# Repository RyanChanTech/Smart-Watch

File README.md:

# Smart-Watch
A smart watch project based off of the ESP32 microcontroller that I work on in my spare time. <br>
More info here: [https://ryanchantech.github.io/project_pages/smartwatch.html](https://ryanchantech.github.io/project_pages/smartwatch.html)

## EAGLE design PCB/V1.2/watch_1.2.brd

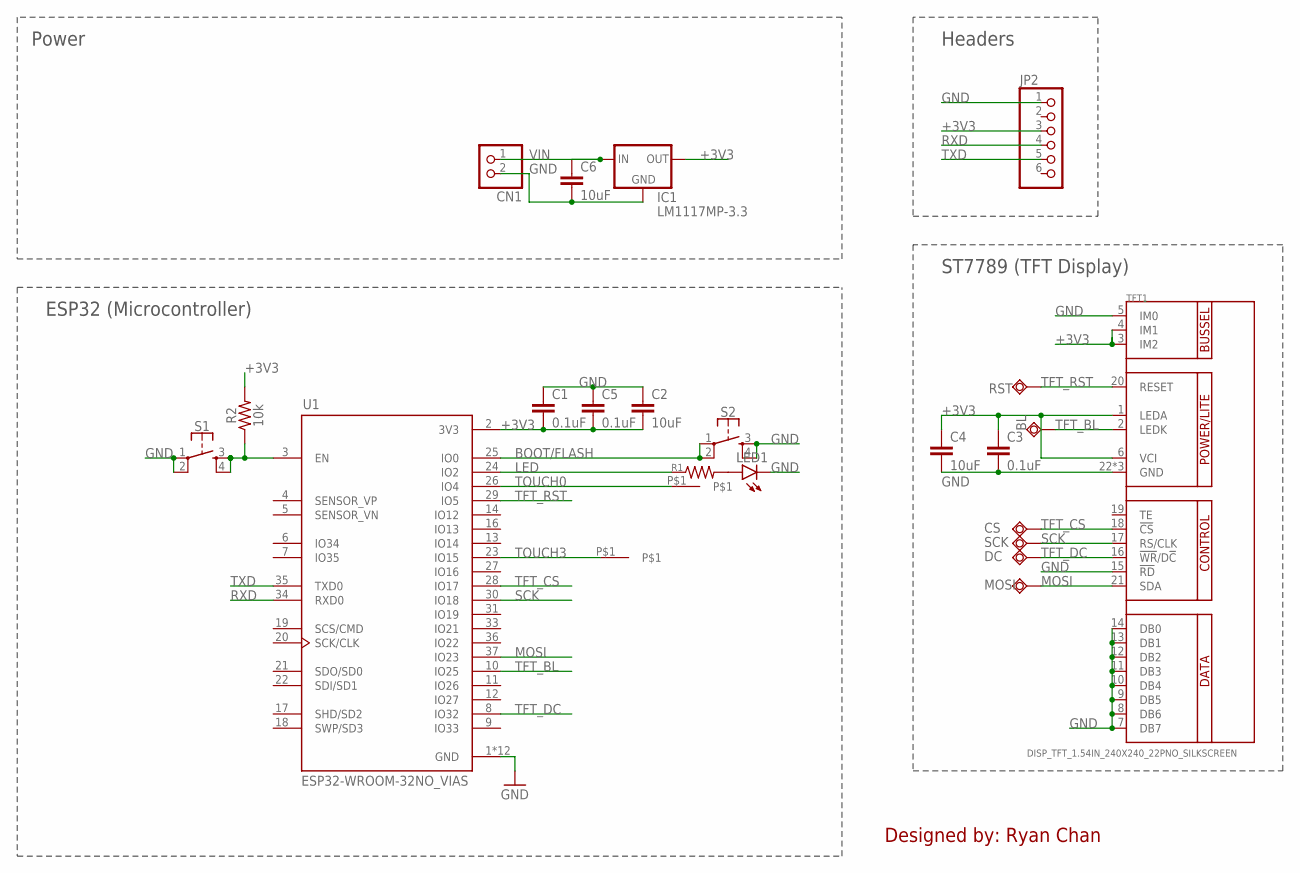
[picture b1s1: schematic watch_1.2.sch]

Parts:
BL: TPSQTP20R; TP20R
C1, C3, C5: 0.1uF; C0603
C2, C4, C6: 10uF; C0603
CN1: JST_2PIN-SMT-RA; JST-PH-2-SMT-RA
CS: TPSQTP20R; TP20R
DC: TPSQTP20R; TP20R
IC1: LM1117MP-3.3; SOT223
JP2: PINHD-1X6CLEAN; 1X06-CLEAN
LED1: LEDCHIPLED_0603; CHIPLED_0603
MOSI: TPSQTP20R; TP20R
R1: R-US_R0603; R0603
R2: 10k; 0603
RST: TPSQTP20R; TP20R
S1, S2: RESET; TACTILE_SWITCH_SMD_4.6X2.8MM
SCK: TPSQTP20R; TP20R
TFT1: DISP_TFT_1.54IN_240X240_22PNO_SILKSCREEN; TFT_1.54IN_240X240_22PIN_NO_SILKSCREEN
U1: ESP32-WROOM-32NO_VIAS; MODULE_ESP32-WROOM-32_NO_VIAS
U$1, U$2: CAPACITIVE_PAD_1

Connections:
+3V3: C1.2, C2.2, C3.1, C4.1, C5.2, IC1.2 (OUT), IC1.4 (OUT), JP2.3, R2.2, TFT1.1 (LEDA), TFT1.3 (IM2), TFT1.4 (IM1), TFT1.6 (VCI), U1.2 (3V3)
BOOT/FLASH: S2.1, S2.2, U1.25 (IO0)
CHIP_PU: R2.1, S1.3, S1.4, U1.3 (EN)
GND: C1.1, C2.1, C3.2, C4.2, C5.1, C6.2, CN1.2 (1), IC1.1 (GND), JP2.1, LED1.C, S1.1, S1.2, S2.3, S2.4, TFT1.5 (IM0), TFT1.7 (DB7), TFT1.8 (DB6), TFT1.9 (DB5), TFT1.10 (DB4), TFT1.11 (DB3), TFT1.12 (DB2), TFT1.13 (DB1), TFT1.14 (DB0), TFT1.15 (!RD), TFT1.22 (GND), TFT1.SUPPORT1 (GND), TFT1.SUPPORT2 (GND), U1.1 (GND), U1.15 (GND), U1.38 (GND), U1.39_1 (GND), U1.39_2 (GND), U1.39_3 (GND), U1.39_4 (GND), U1.39_5 (GND), U1.39_6 (GND), U1.39_7 (GND), U1.39_8 (GND), U1.39_9 (GND)
LED: R1.1, U1.24 (IO2)
MOSI: MOSI.TP, TFT1.21 (SDA), U1.37 (IO23)
unnamed: LED1.A, R1.2
RXD: JP2.4, U1.34 (RXD0)
SCK: SCK.TP, TFT1.17 (RS/CLK), U1.30 (IO18)
TFT_BL: BL.TP, TFT1.2 (LEDK), U1.10 (IO25)
TFT_CS: CS.TP, TFT1.18 (!CS), U1.28 (IO17)
TFT_DC: DC.TP, TFT1.16 (!WR!/D!C), U1.8 (IO32)
TFT_RST: RST.TP, TFT1.20 (RESET), U1.29 (IO5)
TOUCH0: U1.26 (IO4), U$2.P$1
TOUCH3: U1.23 (IO15), U$1.P$1
TXD: JP2.5, U1.35 (TXD0)
VIN: C6.1, CN1.1 (2), IC1.3 (IN)

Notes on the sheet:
Power
Headers
ESP32 (Microcontroller)
ST7789 (TFT Display)
Designed by: Ryan Chan

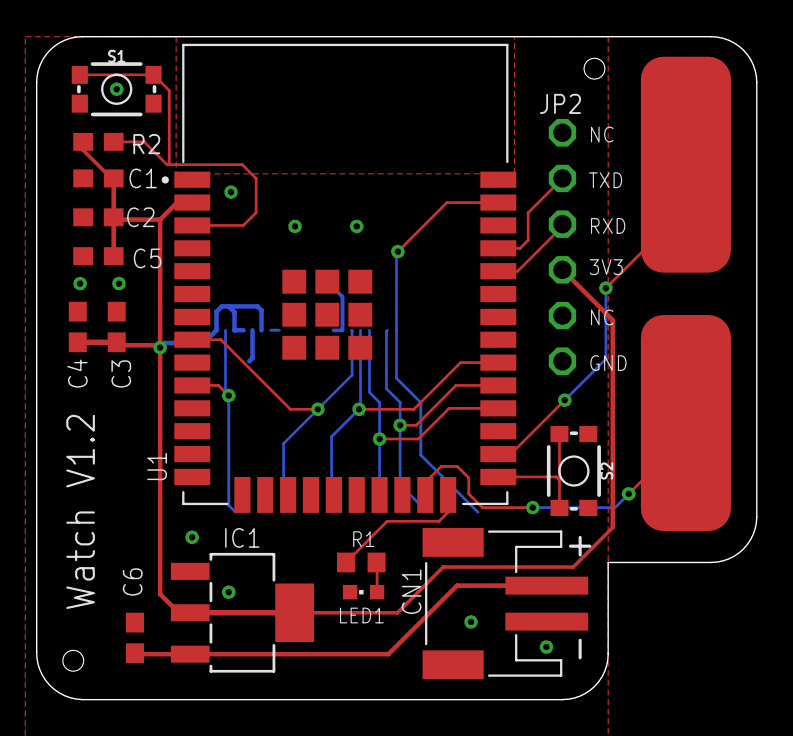
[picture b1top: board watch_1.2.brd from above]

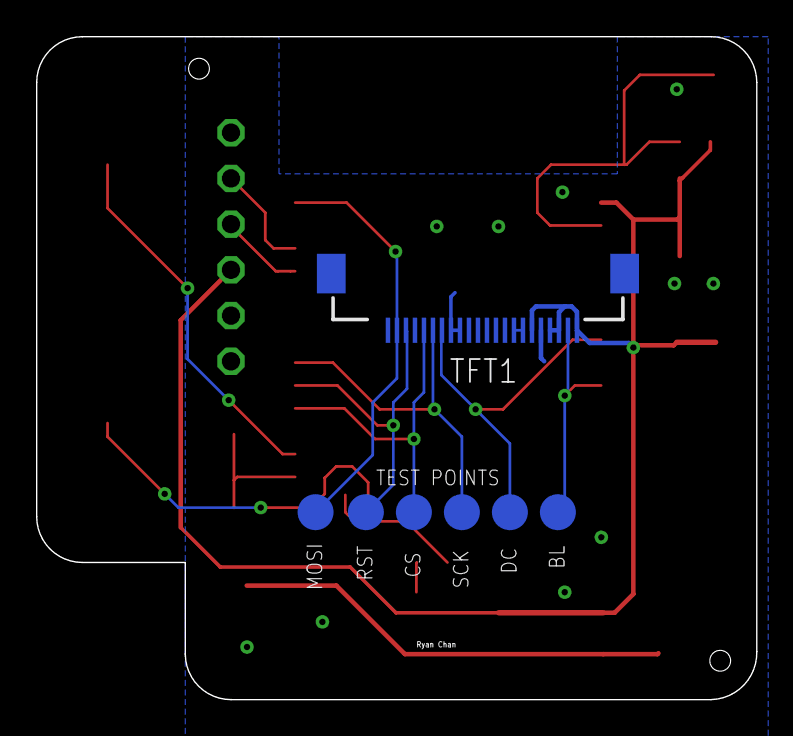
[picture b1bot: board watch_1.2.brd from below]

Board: 2 copper layers, 40.0 x 36.8 mm, 24 parts (6 on the bottom side), 17 nets.

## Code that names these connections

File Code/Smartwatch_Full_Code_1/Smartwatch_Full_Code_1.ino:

// TODO: run new JSON parser with old API link

/*
 * Code written by Ryan Chan
 * WiFi and OpenWeather portion based on code from Random Nerd Tutorials: https://randomnerdtutorials.com/esp32-http-get-open-weather-map-thingspeak-arduino/
 * 
 * To use this, you much install these libraries from the Arduino Library Manager:
 * Arduino_JSON
 * TimeLib
 * Adafruit_GFX
 * Adafruit BusIO
 * Adafruit Zero DMA
 * Adafruit ST7735 and ST7789
 * Adafruit SPIFlash
 */

//include Wifi libraries. to disable, go to places with "@"
#include <WiFi.h>
#include <HTTPClient.h>
#include <ArduinoJson.h>

//include TFT Display libraries
#include <Adafruit_GFX.h>    // Core graphics library
#include <Adafruit_ST7789.h> // Hardware-specific library for ST7789
#include <SPI.h>

#include <TimeLib.h>

//include fonts
#include <Fonts/FreeSansBoldOblique24pt7b.h>
#include <Fonts/FreeSansBoldOblique12pt7b.h>
#include <Fonts/FreeSans12pt7b.h>
#include <Fonts/FreeSansOblique9pt7b.h >
#include <Fonts/FreeSansOblique12pt7b.h >

const char* ssid = "yourWifiNameHere";
const char* password = "yourPasswordHere";

// Your Domain name with URL path or IP address with path
String openWeatherMapApiKey = "your API key here";

// Replace with your country code and city
String latitude = "your latitude here";
String longitude = "your longitude here";

int weatherUpdateInterval = 30; // the number of minutes before the weather data automatically updates

const int TFT_CS = 17;
const int TFT_RST = 5;
const int TFT_DC = 32;
const int TFT_BL = 25;

Adafruit_ST7789 tft = Adafruit_ST7789(TFT_CS, TFT_DC, TFT_RST);

unsigned long last_time;

String weekdays[] = {"Monday","Tuesday","Wednesday","Thursday","Friday","Saturday","Sunday"};

int seconds = 0;
int minutes = 0;
int hours = 0;
int days = 0;

void calculate_times(){
  if(seconds == 60){
    minutes++;
    seconds = 0;
  }
  
  if( minutes == 60 ){
    hours++;
    minutes = 0;
  }

  if(hours == 24){
    days++;
    hours = 0;
  }
}

// prepending 0's needs... alot of work..
String getFormattedHHMM(){
  String formatted_time = "";
  
  if(hours < 10){
    formatted_time += "0";
  }
  formatted_time += hours;
  formatted_time += ":";

  if(minutes < 10){
    formatted_time += "0";
  }
  formatted_time += minutes;

  return formatted_time;
}

String getFormattedSS(){
  String formatted_time = ":";
  if(seconds < 10){
    formatted_time += "0";
  }
  formatted_time += seconds;
  return formatted_time;  
}

//@
void initWifi(){
  WiFi.begin(ssid, password);
  Serial.println("Connecting to Wifi");
  while(WiFi.status() != WL_CONNECTED) {
    delay(500);
    Serial.print(".");
  }
  Serial.println("");
  Serial.print("Connected to WiFi network with IP Address: ");
  Serial.println(WiFi.localIP());
}

String httpGETRequest(const char* serverName) {
  HTTPClient http;
    
  // Your IP address with path or Domain name with URL path 
  http.begin(serverName);
  
  // Send HTTP POST request
  int httpResponseCode = http.GET();
  
  String payload = "{}"; 
  
  if (httpResponseCode>0) {
    Serial.print("HTTP Response code: ");
    Serial.println(httpResponseCode);
    payload = http.getString();
  }
  else {
    Serial.print("Error code: ");
    Serial.println(httpResponseCode);
  }
  // Free resources
  http.end();

  return payload;
}

void setup() {
  // Initialize Serial
  Serial.begin(115200);

  // Initialize TFT display
  tft.init(240, 240);
  tft.fillScreen(ST77XX_BLACK);

  
  // Initialize Wifi@
  tft.setCursor(10, 75);
  tft.setTextColor(ST77XX_WHITE);
  tft.setFont(&FreeSans12pt7b);
  tft.print("Connecting to WiFi...");
  initWifi();
  tft.fillScreen(ST77XX_BLACK);

  last_time = millis();
}

boolean firstRun = true;

void loop() {
  // Keep track of updates
  boolean updateHHMM = false; // update HH:MM (hours:minutes)
  boolean updateSS = false; // update :SS (seconds) 
  boolean updateWeather = false;
  boolean updateDate = false;
  
  int delta = millis() - last_time;
  if(delta >= 999){
    seconds++;
    last_time = millis();
    calculate_times();

    updateSS = true;

    if(seconds == 0 || firstRun){
      updateHHMM = true;
    }

    if( ((hours == 0) && (seconds == 0)) || firstRun){
      updateDate = true;
    }

    if( ((minutes % weatherUpdateInterval == 0) && (seconds == 0)) || firstRun){
      updateWeather = true;
    }
    
    firstRun = false;
  }

  // Display Date
  if(updateDate){
    tft.setTextWrap(true);
    tft.fillRect(10,0,200,30,ST77XX_BLACK);
    tft.setCursor(10, 20);
    tft.setFont(&FreeSans12pt7b);
    tft.setTextColor(ST77XX_WHITE);
    tft.print(weekdays[days%7]);
  }

  // Display HH:MM (hours:minutes)
  if(updateHHMM){
    tft.fillRect(10,30,130,70,ST77XX_BLACK);
    tft.setCursor(10, 75);
    tft.setTextColor(ST77XX_WHITE);
    tft.setFont(&FreeSansBoldOblique24pt7b);
    tft.print(getFormattedHHMM());
    updateHHMM = false;
  }

  // Display :SS (:seconds)
  if(updateSS){
    tft.fillRect(135,30,50,70,ST77XX_BLACK);
    tft.setCursor(135, 75);
    tft.setTextColor(ST77XX_WHITE);
    tft.setFont(&FreeSansBoldOblique12pt7b);
    tft.print(getFormattedSS());
    updateSS = false;
  }

  
  // Get Weather Data@
  if(updateWeather && (WiFi.status() == WL_CONNECTED)){
      //String serverPath = "http://api.openweathermap.org/data/2.5/weather?q=" + yourCity + "," + yourCountryCode + "&APPID=" + openWeatherMapApiKey;
      String serverPath = "http://api.openweathermap.org/data/2.5/weather?q=Scranton,US&APPID=da7b0960d86381f11c5f300c2b546bb1";
      //String serverPath = "https://api.openweathermap.org/data/2.5/onecall?lat=" + latitude + "&lon=" + longitude + "&appid=" + openWeatherMapApiKey;

      String jsonBuffer = httpGETRequest(serverPath.c_str());
      StaticJsonDocument<21000> doc;
      deserializeJson(doc, jsonBuffer);
  
      // Display Humidity
      tft.setCursor(160,170);
      tft.setFont(&FreeSansOblique12pt7b);
      tft.setTextColor(ST77XX_WHITE);
      int currentWeather = doc["main"]["temp"];
      tft.print(currentWeather);
      tft.drawCircle(185, 165, 30, ST77XX_CYAN);
      tft.drawCircle(185, 165, 29, ST77XX_CYAN);
      tft.drawCircle(185, 165, 28, ST77XX_CYAN);

      unsigned long epochTime = doc["current"]["dt"];
      Serial.println(day(epochTime));
      Serial.println(month(epochTime));
      Serial.println(year(epochTime));
      Serial.println(hour(epochTime));
      Serial.println(minute(epochTime));
      Serial.println(second(epochTime));
      
  }
  
}

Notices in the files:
parts and their libraries:
SparkFun-Switches: Licensing: Creative Commons ShareAlike 4.0 International - https://creativecommons.org/licenses/by-sa/4.0
